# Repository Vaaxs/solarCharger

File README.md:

# Solar USB-C Charger

A solar charge controller with MPPT and a 5V USB-C output. You wire a 6V solar panel
into one terminal block and a 1S lithium pack into the other, and it charges the pack
at up to 2.4A while holding the panel at the voltage where it puts out the most power,
then boosts back up to 5V for the USB port.

2 layer board, 90 x 60mm, 30 components, done in KiCad 10.

## Why I made it

Around 700 million people don't have reliable electricity, but phones are basically
everywhere, so a solar charger is one of the few things you can build where the problem
and the thing you're making are both real.

The part that makes this worth building instead of just buying one is the MPPT. A solar
panel has one specific voltage where it gives you the most power, and a dumb charger
ignores that and just pulls the panel down until it stalls out. You end up losing a big
chunk of what the panel could have given you, and it gets worse in weak light, which is
when you actually need it. This board watches the panel voltage through a divider and
holds it at that point instead.

I also didn't want it tied to one specific panel. Anything in the input range works, so
someone with a different panel can still use the board.

## How it works

```
solar panel --> P1 --> CN3791 MPPT buck charger --> P2 --> 1S3P 18650 pack
                         (Q1, L1, D1, R5)                        |
                                                                 v
                           USB-C out <-- TPS61023 boost <-- SW1 enable
                              U3            (U2, L2)
```

U1 is the CN3791, a buck MPPT charger made for solar. It holds the panel at its maximum
power point and does CC/CV charging into the pack. Q1 is the high side switch for the
buck and R5 sets the charge current, since the chip regulates to 120mV across it.

U2 is the TPS61023, which takes the single cell back up to 5V. SW1 turns it on and off
so the board isn't draining the pack when nothing is plugged in.

U3 is the USB-C receptacle. All four VBUS contacts and all four ground contacts are
wired, which is how the current gets shared instead of going through one pin.

### The numbers and where they come from

| what | value | set by |
|---|---|---|
| MPPT setpoint | 5.51V | 1.205 x (1 + R1/R2), R1 357k, R2 100k |
| Panel you need | about 6.9V Voc, 11W or more | setpoint divided by 0.8 |
| Charge current | 2.4A | 120mV / R5, R5 is 0.05 ohm |
| Output voltage | 5.06V | 0.595 x (1 + R14/R15), R14 750k, R15 100k |
| CC pull ups | 56k | R9 and R16, which is what tells a phone it can draw default USB power |

If you want to use a different panel, change R1 and R2. If you want a different charge
current, change R5.

## Pictures

Schematic:

PCB:

The buck switching loop, with Q1, D1 and L1 kept as tight as I could get them and each
ground return taking its own via right at the pad:

The boost section around U2 and L2:

Bottom layer with the ground pour:

3D:

## What's in this repo

```
README.md                      this
JOURNAL.md                     build log with everything that went wrong
BOM.csv                        parts list with links
hardware/
  Solar_charger_3.kicad_pro    project file
  Solar_charger_3.kicad_sch    schematic
  Solar_charger_3.kicad_pcb    board
  solar-charger.pretty/        footprints for the 4 parts KiCad doesn't have
  solar-charger.3dshapes/      3D models for those same parts
  gerbers.zip                  manufacturing files
images/                        screenshots
```

## How to build one

### Order the board

Send hardware/gerbers.zip to any fab. 2 layer, 1.6mm, 1oz copper, HASL or ENIG. The
tightest copper gap on the board is 0.150mm which is inside JLCPCB's 0.127mm minimum so
you don't need anything special.

### Order the parts

Everything is in BOM.csv with links. Get spares of U1, U2 and U3, those are the three
most likely to get wrecked by a bad solder joint.

### Solder it

Do U1 and U2 first while the board is still empty, they're the hardest. U2 is a SOT-563
with 0.5mm pitch so check it under magnification for bridges after. Then all the
resistors and capacitors, then Q1, D1, L1 and L2. Q1's tab needs enough heat to actually
wet. Then U3, and remember the four shield posts are through hole and carry ground. Then
P1, P2 and SW1 last since they're through hole.

### Build the battery pack

Three 18650 cells in parallel with one 1S BMS across the whole pack.

Use unprotected cells for this. If you parallel three cells that each have their own
protection board, the boards don't coordinate with each other and they fight. One BMS for
the pack is the right way to do it.

### Test it before you connect a battery

Check P1 and P2 for shorts between + and - first. Then put a bench supply on P1 at 6V
with the current limit at 500mA. The board should only draw a few mA. Check that U1 pin
9 reads your input voltage, and that U1 pin 6 sits near 1.205V once the loop is
regulating.

Only after that, connect the pack to P2 with SW1 off. Then switch it on and measure the
USB-C output, you should get 5.0V give or take 0.1V.

### Mount it

Four M3 holes, 4mm in from each corner. It's meant to bolt onto the back of the panel.

## Wiring

P1 pin 1 is panel +, pin 2 is panel -. P2 pin 1 is pack +, pin 2 is pack -.

The panel and the battery are not on the board. They're external and they wire into the
two screw terminals.

## Known issues

The board hasn't been fabricated or tested yet, everything here is verified in KiCad
only.

Three of the part number fields in the schematic are stale and don't match the
footprint. L1's MPN field names a 4x4mm 1.5A inductor when the correct one is in the
Value field, SW1's MPN names a completely different switch, and U3's LCSC code needs
checking against the XKB footprint. Order from BOM.csv and not from those fields.

There are four cosmetic silkscreen warnings left in DRC that don't affect anything
electrically.

There's no reverse polarity protection on P1, so wire the panel the right way round.

No enclosure yet, and no battery percentage readout. Both are below.

## What I want to add

A fuel gauge board. A MAX17048 across the pack with a small OLED, taking power and I2C
off the P2 terminals so the main board doesn't have to change at all. It'd sit behind a
momentary button, because an OLED left on all the time would quietly eat whatever the
panel is bringing in.

An I-V curve tracer, so I can actually measure a panel's real maximum power point with a
swept load and a current sensor, and then check that the CN3791 is parking on it instead
of just assuming it does.

## Credits

U1 is the Consonance CN3791 and U2 is the TI TPS61023. Both were designed in from their
datasheets.

Footprints and 3D models come from the KiCad standard libraries, except the terminal
blocks, the slide switch and the USB-C connector, which are in
hardware/solar-charger.pretty and hardware/solar-charger.3dshapes in this repo.

## License

MIT

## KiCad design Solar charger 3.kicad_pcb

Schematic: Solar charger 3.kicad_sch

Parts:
C1: 100nF; C_0805_2012Metric
C2: 220nF; C_0805_2012Metric
C5: 22uF; C_0805_2012Metric
C6, C7: 10uF/25V; C_1206_3216Metric
C8: 22uF; C_1206_3216Metric
C9: 10uF; C_0805_2012Metric
D1: SS34_C8678; D_SMA; MPN SS34; LCSC C8678
L1: 10uH SRN8040TA-100M; L_Bourns_SRN8040TA; MPN SWPA4030S100MT; LCSC C38117
L2: 2.2uH NR4018T2R2M; L_Taiyo-Yuden_NR-40xx; MPN SMNR4020-2.2UH; LCSC C135262
LED1: KT-0603R; LED_0603_1608Metric; MPN KT-0603R; LCSC C2286
LED2: LED (yellow-green); LED_0805_2012Metric; MPN 发光二极管（黄绿色）; LCSC C28105
P1, P2: WJ25C-B-2P; TerminalBlock_Wuerth_691311400102_P7.62mm; MPN WJ25C-B-7.62-02P-13-00A; LCSC C8422
Q1: AOD4185; TO-252-3_TabPin2; MPN AOD4185; LCSC C2564
R1: 357k; R_0805_2012Metric
R2, R12, R15: 100k; R_0805_2012Metric
R3, R4: 1k; R_0805_2012Metric
R5: 0.05R; R_2512_6332Metric
R9, R16: 56k; R_0805_2012Metric
R14: 750k; R_0805_2012Metric
R17: 120R; R_0805_2012Metric
SW1: OS102011MS2Q; SW_Slide_1P2T_CK_OS102011MS2Q; MPN SSSS811101; LCSC C109335
U1: CN3791; SSOP-10_3.9x4.9mm_P1.00mm; MPN CN3791; LCSC C154992
U2: TPS61023DRLR; SOT-563; MPN TPS61023DRLR; LCSC C919459
U3: USB-C 16P; USB_C_Receptacle_XKB_U262-16XN-4BVC11; MPN USB-TYPE-C-019; LCSC C2927039

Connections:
+5V: C5.1, R9.1, R14.1, R16.1, U2.6 (VOUT), U3.A4, U3.A9, U3.B4, U3.B9
CHRG_STATE: LED1.2 (K), U1.3 (~CHRG)
COM: C2.1, U1.5 (COM)
CSP: L1.2, R5.1, U1.8 (CSP)
DONE_STATE: LED2.1 (K), U1.4 (~DONE)
DRV: Q1.1 (G), U1.10 (DRV)
EN_BOOST: R12.1, SW1.1, U2.2 (EN)
FB: R14.2, R15.1, U2.1 (FB)
GND: C5.2, C6.2, C7.2, C8.2, C9.2, D1.2 (A), P1.2, P2.2, R2.2, R12.2, R15.2, R17.2, U1.2 (GND), U2.4 (GND), U3.A1, U3.A12, U3.B1, U3.B12, U3.S1 (1)
unnamed: C2.2, R17.1
unnamed: D1.1 (K), L1.1, Q1.2 (D)
unnamed: LED1.1 (A), R3.2
unnamed: LED2.2 (A), R4.2
unnamed: R9.2, U3.B5
unnamed: R16.2, U3.A5
unnamed: R1.2, R2.1, U1.6 (MPPT)
unnamed: L2.2, U2.5 (SW)
VBAT: C8.1, C9.1, L2.1, P2.1, R5.2, SW1.2, U1.7 (BAT), U2.3 (VIN)
VG: C1.2, U1.1 (VG)
VIN_SOLAR: C1.1, C6.1, C7.1, P1.1, Q1.3 (S), R1.1, R3.1, R4.1, U1.9 (VCC)

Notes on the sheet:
PROTOFLOW_REGION:eyJpZCI6ImZpbmFsLXNlY3Rpb24tN2VmNmU0ZjEyYzEzYjk0OSIsIm5hbWUiOiJTb2xhciBNUFBUIENoYXJnZXIiLCJ4MSI6MTkwLjUsInkxIjozNTUuNiwieDIiOjE2NjMuNywieTIiOjE4NzkuNjAwMDAwMDAwMDAwMSwiY29sb3IiOjQyODMyNjkzMjUsImRlc2NyaXB0aW9uIjpudWxsLCJjb21wb25lbnRJZHMiOlsiMDA3ZmI2MDQtN2YyOC00YzA1LTk3ZGMtOTU5OTRkNm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
Status LEDs
56k Rp on CC1/CC2: default USB power
VG bypass
PROTOFLOW_REGION:eyJpZCI6ImZpbmFsLXNlY3Rpb24tODAzZWRlYmQ2ZGFiZTA1MCIsIm5hbWUiOiJVU0ItQyBQb3dlciBPdXRwdXQiLCJ4MSI6MzI2My44OTk5OTk5OTk5OTk2LCJ5MSI6NDE5LjEsIngyIjozODEwLjAsInkyIjoxMDU0LjEsImNvbG9yIjo0MjkxNDAyNTUyLCJkZXNjcmlwdGlvbiI6bnVsbCwiY29tcG9uZW50SWRzIjpbIjA3NzlmN2RlLWNmOWMtNDNkNS04YTJhLWMxNWVkZW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
5V Boost Converter
Vout = 0.595 x (1 + R14/R15) = 5.06 V
COM compensation
Solar MPPT Charger
1S3P Li-ion pack (3x 18650) via external 1S BMS
Slide to pin 1 = ON, pin 3 = OFF
USB-C Power Output
PROTOFLOW_REGION:eyJpZCI6ImZpbmFsLXNlY3Rpb24tNGY1Mzk1ZWU3Zjc3ZWM5NCIsIm5hbWUiOiI1ViBCb29zdCBDb252ZXJ0ZXIiLCJ4MSI6MTkzMC4zOTk5OTk5OTk5OTk5LCJ5MSI6NDE5LjEsIngyIjozMDYwLjcsInkyIjo5NjUuMTk5OTk5OTk5OTk5OSwiY29sb3IiOjQyODkzNjAwNzcsImRlc2NyaXB0aW9uIjpudWxsLCJjb21wb25lbnRJZHMiOlsiYTBlOGQ0OGQtNGMzYi00YWRhLT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
SOLAR PANEL IN
PROTOFLOW_REGION:eyJpZCI6ImZpbmFsLXNlY3Rpb24tMzUyMDgwMmZkZGIzY2FiMyIsIm5hbWUiOiJCYXR0ZXJ5IEJvb3N0IEVuYWJsZSIsIngxIjoxOTU1LjgwMDAwMDAwMDAwMDIsInkxIjoxMDI4LjcsIngyIjoyNjE2LjIsInkyIjoxNTExLjMsImNvbG9yIjo0MjgyNDI3NTA0LCJkZXNjcmlwdGlvbiI6bnVsbCwiY29tcG9uZW50SWRzIjpbIjAwNGQ5YThiLTg1NWQtNGUxMS05ZGVhLWVmNz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
Battery Boost Enable

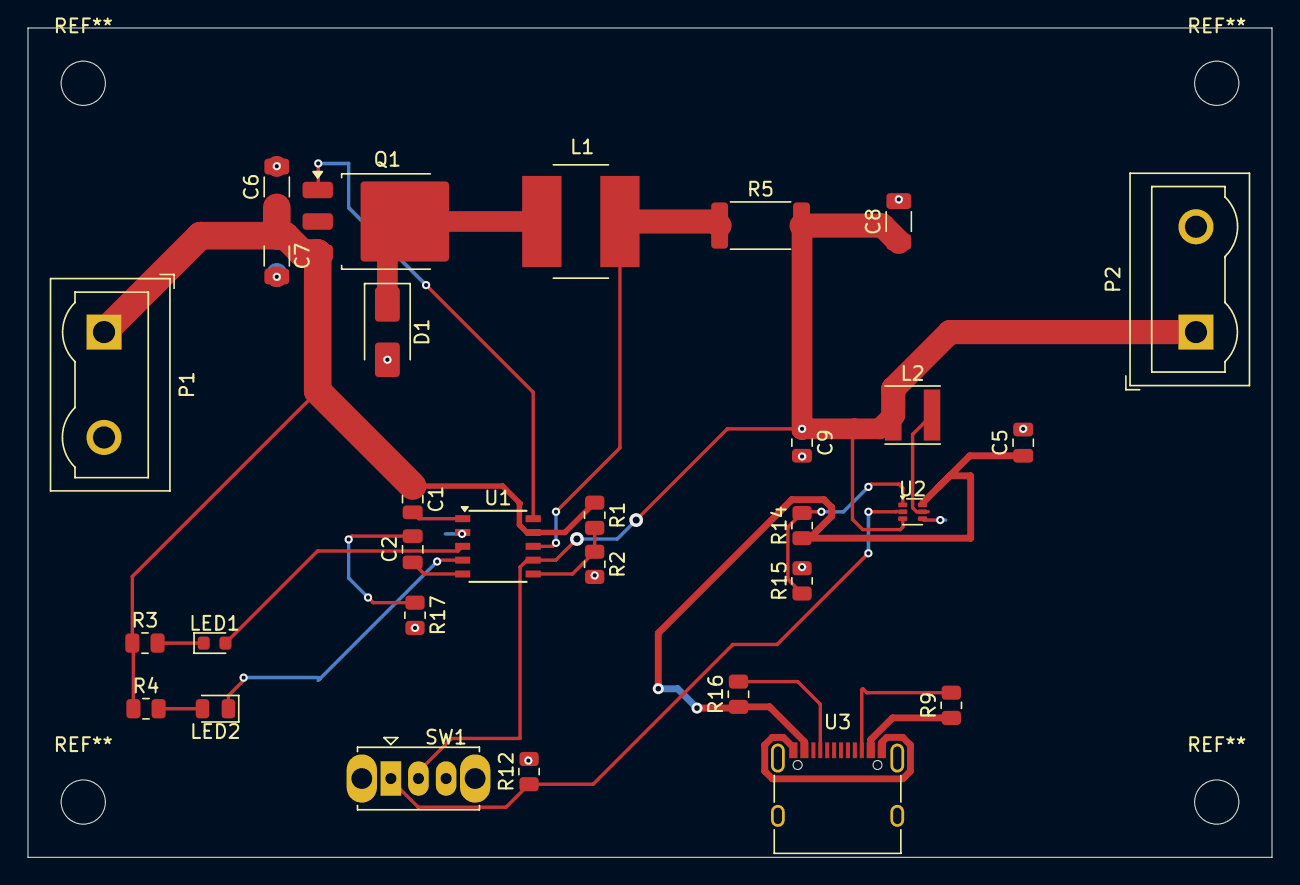
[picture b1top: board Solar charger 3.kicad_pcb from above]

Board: 2 copper layers, 90.0 x 60.0 mm, 30 parts (0 on the bottom side), 20 nets.

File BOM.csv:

Ref,Qty,Value,Package,Manufacturer Part,LCSC,Link,Unit Price (USD),Ext Price (USD),Notes
C1,1,100nF 50V X7R,0805,,,https://lcsc.com/search?q=100nF+0805+X7R,,,VG bypass
C2,1,220nF 50V X7R,0805,,,https://lcsc.com/search?q=220nF+0805+X7R,,,COM compensation
C5,1,22uF 10V X5R,0805,,,https://lcsc.com/search?q=22uF+0805+X5R,,,Boost output
C6,1,10uF 25V X5R,1206,,,https://lcsc.com/search?q=10uF+1206+25V+X5R,,,Panel input
C7,1,10uF 25V X5R,1206,,,https://lcsc.com/search?q=10uF+1206+25V+X5R,,,Panel input
C8,1,22uF 25V X5R,1206,,,https://lcsc.com/search?q=22uF+1206+25V+X5R,,,Battery bulk
C9,1,10uF 10V X5R,0805,,,https://lcsc.com/search?q=10uF+0805+X5R,,,Boost input
D1,1,SS34 40V 3A Schottky,SMA,SS34,C8678,https://www.lcsc.com/product-detail/C8678.html,,,Buck freewheel diode
L1,1,10uH 3.1A shielded,SRN8040 8x8x4mm,SRN8040TA-100M,,https://www.bourns.com/products/magnetic-products/power-inductors,,,Buck inductor. Must be 8x8mm and rated above 2.4A
L2,1,2.2uH shielded,NR4018 4x4mm,NR4018T2R2M,C135262,https://www.lcsc.com/product-detail/C135262.html,,,Boost inductor
LED1,1,Red LED,0603,KT-0603R,C2286,https://www.lcsc.com/product-detail/C2286.html,,,Charging indicator
LED2,1,Yellow-green LED,0805,,C28105,https://www.lcsc.com/product-detail/C28105.html,,,Charge complete indicator
P1,1,2-pin screw terminal 7.62mm,THT,WJ25C-B-7.62-02P,C8422,https://www.lcsc.com/product-detail/C8422.html,,,Solar panel input
P2,1,2-pin screw terminal 7.62mm,THT,WJ25C-B-7.62-02P,C8422,https://www.lcsc.com/product-detail/C8422.html,,,Battery pack
Q1,1,AOD4185 P-MOSFET -40V -40A,TO-252,AOD4185,C2564,https://www.lcsc.com/product-detail/C2564.html,,,Buck high-side switch
R1,1,357k 1%,0805,,,https://lcsc.com/search?q=357k+0805+1%25,,,MPPT divider upper
R2,1,100k 1%,0805,,,https://lcsc.com/search?q=100k+0805+1%25,,,MPPT divider lower
R3,1,1k,0805,,,https://lcsc.com/search?q=1k+0805,,,LED1 series
R4,1,1k,0805,,,https://lcsc.com/search?q=1k+0805,,,LED2 series
R5,1,0.05R 1% 1W,2512,,,https://lcsc.com/search?q=0.05R+2512+1%25,,,Charge current sense. Sets 2.4A
R9,1,56k 1%,0805,,,https://lcsc.com/search?q=56k+0805+1%25,,,CC2 pull-up
R12,1,100k,0805,,,https://lcsc.com/search?q=100k+0805,,,Boost enable pull-down
R14,1,750k 1%,0805,,,https://lcsc.com/search?q=750k+0805+1%25,,,Boost feedback upper
R15,1,100k 1%,0805,,,https://lcsc.com/search?q=100k+0805+1%25,,,Boost feedback lower
R16,1,56k 1%,0805,,,https://lcsc.com/search?q=56k+0805+1%25,,,CC1 pull-up
R17,1,120R,0805,,,https://lcsc.com/search?q=120R+0805,,,COM compensation
SW1,1,SPDT slide switch THT,OS102 series,OS102011MS2Q,,https://www.ckswitches.com/products/switches/product-details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,,,Boost on/off
U1,1,CN3791 MPPT charger,SSOP-10,CN3791,C154992,https://www.lcsc.com/product-detail/C154992.html,,,Solar charge controller
U2,1,TPS61023 boost converter,SOT-563,TPS61023DRLR,C919459,https://www.lcsc.com/product-detail/C919459.html,,,5V boost
U3,1,USB-C receptacle 16-pin,SMD + 4 THT posts,XKB U262-16XN-4BVC11,C319148,https://www.lcsc.com/product-detail/C319148.html,,,5V output
PCB,1,2-layer 90x60mm 1.6mm FR4,,,,https://jlcpcb.com,,,Order 5 minimum
BATT,3,18650 Li-ion cell unprotected,,,,https://lcsc.com,,,1S3P pack. Must be UNPROTECTED cells
BMS,1,1S Li-ion BMS 10A,,,,https://lcsc.com,,,One BMS for the whole pack
PANEL,1,6V 12W solar panel,,,,,,,~6.9V Voc. Not on the board
SCREW,4,M3 x 8mm screw + nut,,,,,,,Board mounting
,,,,,,,TOTAL,,Fill unit prices then sum the Ext Price column
